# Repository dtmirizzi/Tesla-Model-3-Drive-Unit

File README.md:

# Tesla-Model-3-Drive-Unit
Open Source logic board for the Tesla Model 3 rear drive unit. PCB Files in DesignSpark 9 and Kicad 8 format.Based on the inverter designed by Johannes Heubner using FOC control.
<br>

<br>
13/03/20 : Added CAN logs from both CAN busses from the rear drive unit inverter powered on the bench.

04/05/20 : Added pdf schematic and board layout for the V1 logic board design. Untested as of this date. Given recent developments the design files will not be released at this time. For more information see : <br>
https://openinverter.org/forum/viewtopic.php?f=10&t=575

26/07/20 : After initial testing of V1 in a rear drive unit inverter some issues were found. V2 now released. Changes :

-Added resolver signal preconditioning circuit. Resolver signal needs to be amplified to 1v p-p and offset to 1.6v before feeding to the Tesla resolvver power amp.

-Added opamp to combine differential HV voltage measurement to unipolar.

-Deleted Tagconnect Jtag.

-Added 3v3 pin for single wire programming via st-link.

-Added solder jumper for optional single 5v power supply.

Please note design source files will be only available via Patreon for a period of time:

https://www.patreon.com/evbmw

02/10/20 : V2 board now fully tested in an M3 Rear drive unit and working very well on the bench.
<br>At this time I have decided to do a full opensource release of all design sources:)
<br>More updates and video to following including testing in a M3 front DU.

18/11/20 : Uploaded spreadsheet work in progress for mapping the pin assignments of the TMS320F28377D MCU.

21/11/20 : Discovered an eeprom on the back of the pcb. Logic analyser captures uploaded. All logic analyser captures made using Saleae logic. Free software available here :https://www.saleae.com/downloads/

02/12/20 : Big thanks to Colin Kidder (https://github.com/collin80) for the explanation of the STGAP1AS SPI gate driver traffic. PDF uploaded to the Gate SPI folder.

11/12/20 : Big thanks again to Colin Kidder (https://github.com/collin80) for the explanation of the TLF SPI power supply traffic. PDF uploaded to the TLF SPI folder.

08/02/21 : We have a new modboard : https://vimeo.com/509198907

08/05/21 : Added V3 modboard pdf schematic and board layout. Turns out Mr.Musk almost made a fool of me....again! 

18/10/21 : Added design files for USB to JTAG adapter board.

19/03/23 : Add first temp sensor calibration data

30/03/23 : Running : https://vimeo.com/809120859

15/08/24 : Added a very early schematic of the gate driver section for use in the PCB replacement project.

24/10/24 : Updated schematic of the gate driver power supply section for use in the PCB replacement project.

17/01/25 : Updated schematic and PCB layout to latest "complete" V1 version.

07/05/25 : First prototypes undergoing test.

28/05/25 : Testing continues. First motor spins :

https://youtu.be/JKbsiIRJ8mo

29/09/25 : V2 board now runs on HV : https://vimeo.com/1122427765

Added V3 Schematic and board layout.

26/10/25 : The V3 works. https://youtu.be/QYh9N8k0tf8

18/11/25 : First in car tests : https://youtu.be/6yrDDHRgUPQ also added pinout diagram.

03/12/25 : Updated 30 pin connector pinout and added a DXF of the OEM board derived from a laser scan.

01/02/26 : Uploaded V3.2 schematic and pcb layout. First order of boards on the way!

26/02/26 : Added capture of the gate driver SPI from a Model 3 front drive unit inverter.

28/02/26 : V3.2 board now undergoing testing.

07/03/26 : I have made the decision to fully opensource the V3.2 design. Almost six years of work in here by myself and others so please respect that.

09/04/26 : An amazing contribution : https://github.com/jrbe/Tesla-Model-3-Current-Sensor-Block
           Prototypes on order.

atopile port: [`ato/`](ato/README.md) describes the V3.2 board as code, organised into modules with one shared gate-driver phase. It is checked pad by pad against the KiCad design and keeps the original layout.

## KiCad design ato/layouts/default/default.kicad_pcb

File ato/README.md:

# M3DU logic board in atopile

An [atopile](https://atopile.io) port of the V3.2 logic board in
`../Design/M3DU_BoardV3_2`. It is the same board, checked pad by pad: the same
798 parts, designators, nets, BOM and hand-routed layout. It is organised into
modules, one per block of the schematic, and the three gate-driver phases share
one `GateDrivePhase` module. See [PLAN.md](PLAN.md) for details and next steps.

## Layout

```
ato.yaml                 atopile project (requires atopile ^0.15.9)
main.ato                 module M3DU: the blocks, power rails and nets between blocks
src/                     one module per schematic block (power/, gate_drive/, sensing/, ...)
parts/<KiCadLib>/        one atopile component per BOM line + its footprint/symbol
layouts/default/         the KiCad board atopile builds into (seeded from the original PCB)
lib/                     footprint + symbol libraries recovered from the KiCad design
reference/netlist.json   reference netlist extracted from the original PCB
reference/addresses.json designator -> atopile address (binds the layout)
tools/                   extraction, code generation, layout seeding and the equivalence check
```

## Build

```bash
uv venv -p 3.14 .venv && . .venv/bin/activate
uv pip install atopile==0.15.9 pandas xlrd

tools/port.sh            # extract -> generate -> seed layout -> ato build -> check
# or, once seeded:
ato build --no-standardize-designators
python tools/restore_layout.py  # put back attributes atopile 0.15.9 drops
python tools/check_netlist.py   # board vs KiCad V3.2: nets + layout
python tools/check_bom.py       # BOM vs the V3.2 JLC BOM
```

`main.ato`, `src/` and `parts/` are generated by `tools/gen_modules.py` (set
`FLAT=1` for a single flat module). The board stays bound to the layout through
the original designators.

`check_netlist.py` exits non-zero unless the built board matches the original:
the same references and pad geometry, the same pad-to-net partition, and every
footprint, track, via and zone in place.

Open `layouts/default/default.kicad_pcb` in KiCad 9 to view or edit the board.
After editing the layout, run `tools/port.sh --no-seed` so your edits are kept.
For now the original KiCad project is still the source of truth: `tools/port.sh`
and CI regenerate everything from it.

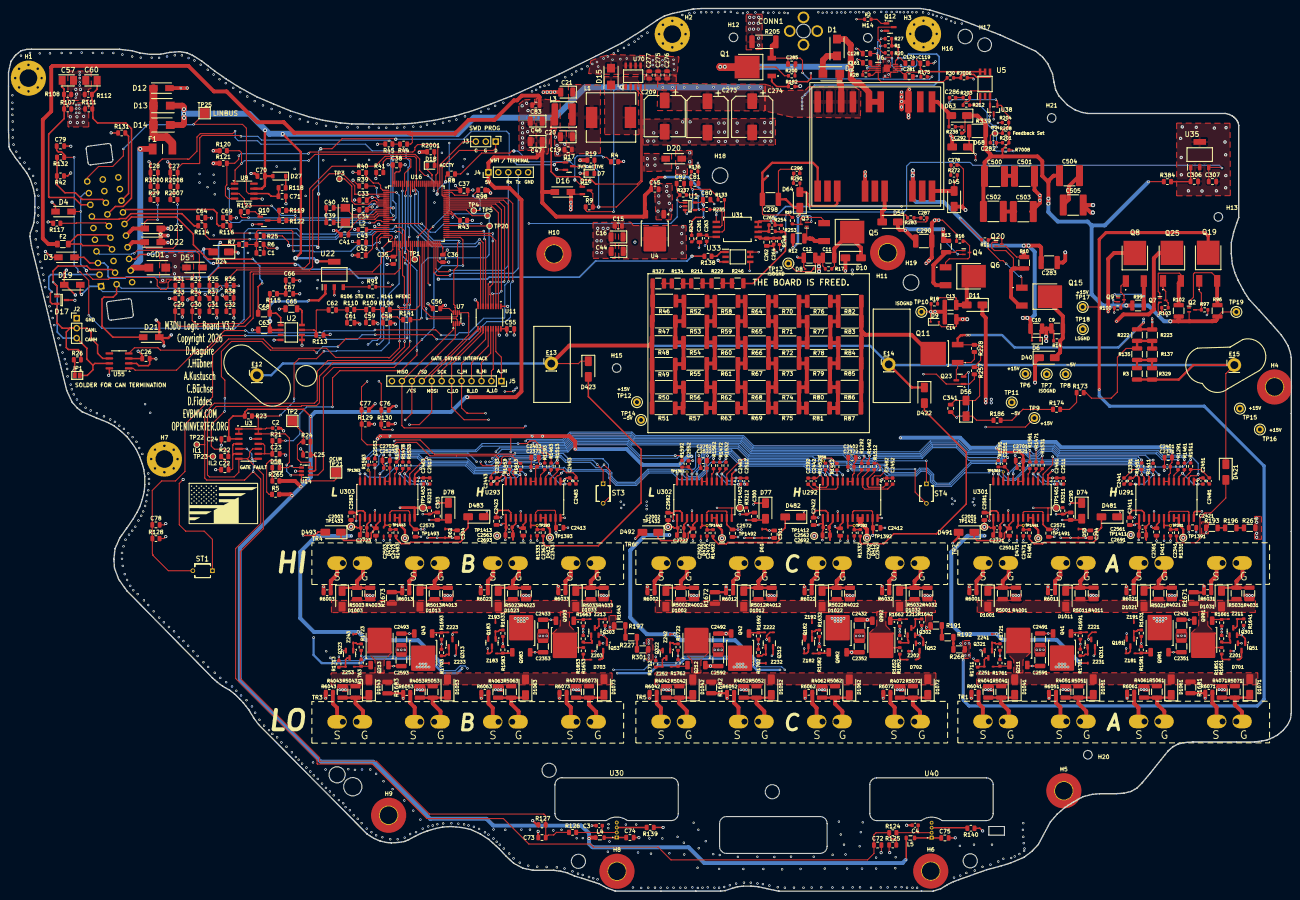
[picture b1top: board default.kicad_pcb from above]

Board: 4 copper layers, 327.6 x 225.4 mm, 797 parts (1 on the bottom side), 394 nets.

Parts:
C1, C306: 1uF; C_0805_2012Metric__v3
C2: 10nF; C_0603_1608Metric__v3
C3, C4, C265: 10nF; C_0603_1608Metric
C9, C10, C11, C12, C13, C14: 2.2uF; C_1210_3225Metric
C15, C19, C22, C24, C25, C27, C28, C34, C35, C36, C56, C70: 1uF; C_0805_2012Metric__v2
C16, C20, C21, C44: 100uF 6.3V; CP_EIA-3528-15_AVX-H__v2
C23, C29, C30, C31, C32, C37, C38, C45, C55, C74, C75, C76, C77, C78, C79, C80, C119, C276, C277, C301, C304, C341, C2361, C2362, C2363, C2411, C2412, C2413, C2421, C2422, C2423, C2501, C2502, C2503, C2571, C2572, C2573, C2581: 1uF; C_0805_2012Metric
C26, C41, C42: 100nF; C_0805_2012Metric
C33, C43, C261: 10uF; C_0805_2012Metric
C39, C40: 22pF; C_0805_2012Metric
C46, C47: 100uF 6.3V; CP_EIA-3528-15_AVX-H
C57: 100uF 6.3V; CAPPM3528X210N
C58, C59, C61, C66, C67: 22nF; C_0805_2012Metric
C60: 100uF 6.3V; CAPPM3528X210N__v2
C62: 22nF; C_0805_2012Metric__v2
C63, C65: 10uF; C_1206_3216Metric__v2
C64, C69, C71, C72: 1nF; C_0805_2012Metric
C68: 10uF; C_1206_3216Metric
C73: 1nF; C_0805_2012Metric__v2
C81, C82: 100pF; C_0805_2012Metric
C83: 1nF; C_0805_2012Metric__v4
C124, C275: 0.1uF; C_0805_2012Metric
C128: 200pF; C_0805_2012Metric
C161: 47nF; C_0805_2012Metric
C209: 100uF 25V; CP_Elec_10x10
C262: 10uF; C_0805_2012Metric__v2
C263, C2001, C2002, C2003, C2371, C2372, C2373, C2521, C2522, C2523, C2561, C2562, C2563: 100nF; C_0603_1608Metric
C264: 100nF; C_0603_1608Metric__v2
C273, C274: 220uF 35V; CP_Elec_10x10
C278, C287, C292, C296, C2341, C2342, C2343, C2471, C2472, C2473: 82pF; C_0603_1608Metric
C281: 330pF; C_0805_2012Metric
C282: 10nF; C_0603_1608Metric__v2
C283, C290, C298: 3.3uF; C_1812_4532Metric
C285: 470pF; C_0805_2012Metric
C286: 22nF; C_0603_1608Metric__v2
C293, C294, C300, C303, C2582, C2583: 2.2uF; C_0805_2012Metric
C307: 10uF; C_0805_2012Metric__v3
C500, C501, C502, C503, C504, C505: 15uF; C_2220_5750Metric
C2351, C2352, C2353, C2431, C2432, C2433, C2491, C2492, C2493, C2591, C2592, C2593: 4.7uF; C_1210_3225Metric
C2391, C2392, C2393, C2451, C2452, C2453, C2461, C2462, C2463, C2481, C2482, C2483, C2511, C2512, C2513, C2551, C2552, C2553: 82pF; C_0603_1608Metric__v2
C2401, C2402, C2403, C2691, C2692, C2693, C2701, C2702, C2703, C2721, C2722, C2723: 4.7uF; C_0805_2012Metric
C2441, C2442, C2443: 470pF; C_0603_1608Metric__v2
CONN1: HV_Hvil; HV_HVIL
D1: 1N5819; DIOM5336X244N__v2
D2: 1N5935B; DIOM5336X244N__v2
D3, D4, D5, D19: SMAJ18CA; DIOM5127X229N
D6, D8: 5V1; D_SOD-323__v2
D7: 3V3 LED; LED_0805_2012Metric
D9: 5V1; D_SOD-323
D10, D40: SS35; D_SMA__v2
D11: SS35; D_SMA
D12: SMAJ18CA; DIONM5127X229N
D13, D14: SS54B; DIOM5336X244N
D15: SS54B; DIOM5336X244N__v2
D16, D22, D23: SMAJ7.0A; DIOM5026X229N
D17: ESDCAN01-2BLY; SOT95P255X150-3N
D18: LED; LED_0805_2012Metric
D20: SMAJ7.0A; DIOM5026X229N__v2
D21: SMAJ18CA; DIOM5127X229N__v2
D24: SMAJ18CA; D_SMA__v3
D27: 1N4148W; D_SOD-123
D45, D64: STPS2H100-Y; D_SMA__v2
D53, D61, D62: G1; D_SOD-323__v3
D54, D63: STPS2H100-Y; D_SMA
D56: 15V; D_SMA__v4
D58: LED; LED_0805_2012Metric__v2
D68: Zener 5V1; D_SMA
D74, D77, D78, D421, D422, D423: VN17; D_SMA
D411, D412, D413, D701, D702, D703: JV; D_SOD-323
D471, D472, D473: JV; D_SOD-323__v3
D481, D482, D483, D491, D492, D493: VN17; D_SMA__v2
D1001, D1002, D1003, D1011, D1012, D1013, D1021, D1022, D1023, D1031, D1032, D1033, D1041, D1042, D1043, D1051, D1052, D1053, D1061, D1062, D1063, D1071, D1072, D1073: 2H2; D_SMA
E12, E13, E14, E15: HV+; M3_HVPOS
F1: JFC2410-0500TS; FUSC6126X280N
F2: 1206L050/24WR; Fuse_1206_3216Metric
GD1: 2051-09-SM-RPLF; DIOM5336X244N
H1, H2, H3, H7: MountingHole_Pad; MountingHole_4.5mm_Pad_Via
H4, H5, H6, H8, H9, H10, H11: MountingHole_Pad; MountingHole_4.5mm_Pad_TopBottom
H12, H14, H15, H21: MountingHole; MountingHole_2.2mm_M2__v2
H13: MountingHole; MountingHole_2.2mm_M2__v3
H16: MountingHole; MountingHole_3.7mm
H17: MountingHole; MountingHole_3.5mm
H18, H19: MountingHole; MountingHole_4mm
H20: MountingHole; MountingHole_2.2mm_M2
J1: Conn_01x30_Male; M3DU_MAINCONN
J2: CAN MON; PinHeader_1x03_P2.54mm_Vertical
J3: M032.54MM; PinHeader_1x03_P2.54mm_Vertical
J4: WiFi Serial Interface; PinHeader_1x05_P2.54mm_Vertical
J5: Conn_01x12_Socket; PinSocket_1x12_P2.54mm_Vertical
JP1: SolderJumper_2_Open; SolderJumper-2_P1.3mm_Open_Pad1.0x1.5mm
L1: 68uH; L_12x12mm_H8mm
L2, L4, L5: 10uH; L_0805_2012Metric
L3: 3uH; L_APV_ANR6020
Q1: IPD50N06S409ATMA2
Q2, Q3, Q4, Q7, Q9, Q20: BC857BT-7-F; SOT50P160X90-3N
Q5, Q6, Q15: NJVMJD127T4G; NVD5117PLT4GVF01__v2
Q8, Q19, Q25: NJVMJD127T4G; NVD5117PLT4GVF01
Q10, Q12: MMBT3904; SOT-23
Q11: FGD3N60LSDTM
Q16, Q17: MMBT3904; SOT-23__v3
Q23: BSS84W; SOT-23__v2
Q41, Q42, Q43, Q981, Q982, Q983: 45P4LLF6; TO-252-2
Q51, Q52, Q53: SG NMOS D; SOT-23
Q181, Q182, Q183: BSS84AK; SOT-23__v2
Q211, Q212, Q213, Q991, Q992, Q993: 3N0408; TO-252-2
Q301, Q302, Q303: BSS138BK; SOT-23__v2
Q311, Q312, Q313: BSS84AK; SOT-23
Q321, Q322, Q323: BSS138BK; SOT-23
R1, R133, R136, R235, R237: 10K; R_0603_1608Metric
R2: 3K3; R_0603_1608Metric
R3, R135, R137, R222, R223, R329: 82K; R_1210_3225Metric
R4: 10K; R_0805_2012Metric__v6
R5: 10K; R_0805_2012Metric__v9
R6: 1K5; R_0805_2012Metric__v3
R7: 4K7; R_0805_2012Metric__v3
R8, R25: 10K; R_0805_2012Metric__v3
R9: 27K; R_0805_2012Metric__v4
R10, R13, R99: 4R99; R_1210_3225Metric
R11, R16, R97, R100, R103: 22K; R_0603_1608Metric
R12, R96, R102: 4R99; R_1210_3225Metric__v2
R14, R17, R18: 4K7; R_0603_1608Metric
R15: 22K; R_0603_1608Metric__v2
R19: 680R; R_0805_2012Metric__v2
R20: 4R7; R_0603_1608Metric
R21, R22, R113, R114, R115, R116, R119, R128, R129, R130: 10K; R_0805_2012Metric__v2
R23, R24, R31, R32, R35, R36, R41: 4K7; R_0805_2012Metric__v2
R26: 120R; R_0805_2012Metric__v2
R27: 300K; R_0603_1608Metric
R28: 33.2K; R_0603_1608Metric__v2
R29, R39, R40, R43, R118, R123, R131, R132, R265, R2007, R2008, R3000: 1K; R_0805_2012Metric__v2
R30: 18K; R_0603_1608Metric
R33, R34, R37, R38: 1K5; R_0805_2012Metric__v2
R42, R44: 47K; R_0805_2012Metric__v2
R45, R122: 3K3; R_0805_2012Metric__v2
R46, R51, R56, R61, R66, R71, R76, R81, R82, R83, R84, R85, R86, R87: 3K9; R_2512_6332Metric
R47, R48, R49, R50, R52, R53, R54, R55, R57, R58, R59, R60, R62, R63, R64, R65, R67, R68, R69, R70, R72, R73, R74, R75, R77, R78, R79, R80: 3K9; R_2512_6332Metric__v2
R91: 1K; R_0603_1608Metric
R98: 1K; R_0805_2012Metric__v3
R106: 3K9; R_0805_2012Metric__v7
R107, R108, R112: 220R; R_0805_2012Metric__v2
R109, R110: 1K8; R_0805_2012Metric__v2
R111: 220R; R_0805_2012Metric
R117: 0R; R_0805_2012Metric__v2
R120, R121, R138: 2K2; R_0805_2012Metric__v2
R124, R126: 3K6; R_0805_2012Metric__v2
R125, R127: 6K2; R_0805_2012Metric__v2
R134, R211, R229, R246, R327: 75K; R_1210_3225Metric
R139, R140: 10k; R_0805_2012Metric__v5
R141: 3K9; R_0805_2012Metric__v8
R173, R174, R186: 50K; R_0805_2012Metric__v4
R175, R1331, R1332, R1333, R1411, R1412, R1413, R1461, R1462, R1463, R1471, R1472, R1473, R1481, R1482, R1483, R7006: 1k; R_0603_1608Metric
R182: 100K; R_0603_1608Metric__v2
R191, R192, R193, R196, R197, R227, R267, R268, R301: 1M; R_1206_3216Metric
R200: 20R; R_0603_1608Metric__v2
R201: 35K6; R_0603_1608Metric
R203, R212: 25K; R_0603_1608Metric
R204: 5K6; R_0603_1608Metric
R205: 0.01R; R_2512_6332Metric_Pad1.40x3.35mm_HandSolder
R208: 39K; R_0603_1608Metric
R228, R257: 100K; R_0805_2012Metric__v2
R238: 80.6R; R_0603_1608Metric__v2
R247, R248: 10R; R_0603_1608Metric
R253: 39R; R_0603_1608Metric
R254: 1K6; R_0603_1608Metric
R272, R283, R291: 80.6R; R_0603_1608Metric
R339: 4K7; R_1812_4532Metric
R384: 0R; R_0805_2012Metric__v4
R1291, R1292, R1293, R1561, R1562, R1563: 680; R_0603_1608Metric
R1451, R1452, R1453, R1511, R1512, R1513, R1531, R1532, R1533, R1641, R1642, R1643, R1711, R1712, R1713: 100; R_0603_1608Metric
R1581, R1582, R1583, R1631, R1632, R1633, R1651, R1652, R1661, R1662, R1663, R1691, R1692, R1693, R1701, R1702, R1703, R1761, R1762, R1763, R1853: 27K; R_0603_1608Metric
R1591, R1592, R1593: 200; R_0603_1608Metric
R1653, R1851, R1852: 470; R_0603_1608Metric
R1671, R1672, R1673: 4K7; R_1210_3225Metric__v2
R1681, R1682, R1683: 4K7; R_1210_3225Metric
R1721, R1722, R1723: 27K; R_0603_1608Metric__v3
R2001: 330R; R_0805_2012Metric__v2
R3211, R3212, R3213: 0R; R_0603_1608Metric
R4001, R4002, R4003, R4011, R4012, R4013, R4021, R4022, R4023, R4031, R4032, R4033, R4041, R4042, R4043, R4051, R4052, R4053, R4061, R4062, R4063, R4071, R4072, R4073: 12; R_1210_3225Metric
R5001, R5002, R5003, R5011, R5012, R5013, R5021, R5022, R5023, R5031, R5032, R5033, R5041, R5042, R5043, R5051, R5052, R5053, R5061, R5062, R5063, R5071, R5072, R5073: 10; R_1210_3225Metric
R6001, R6002, R6003, R6011, R6012, R6013, R6021, R6022, R6023, R6031, R6032, R6033, R6041, R6042, R6043, R6051, R6052, R6053, R6061, R6062, R6063, R6071, R6072, R6073: 0.56R; R_0805_2012Metric
R7008: 2K; R_0603_1608Metric
ST1, ST3, ST4: Thermistor; B59100C0140A070
T1: TDK_VGT; VGT22EPC-200S6A12
TP1, TP3, TP4, TP5, TP22, TP23, TP24: TestPoint; TestPoint_Pad_D1.0mm
TP2, TP21, TP25: TestPoint; TestPoint_Pad_2.5x2.5mm
TP6, TP7, TP8, TP9, TP11, TP12, TP13, TP14, TP15, TP16, TP17, TP18, TP19: TestPoint; TestPoint_Keystone_5000-5004_Miniature
TP10: GND_ISO_C; TestPoint_Keystone_5000-5004_Miniature
TP20: TestPoint_Pad_D1.0mm
TP58, TP291, TP292, TP293, TP1361, TP1362, TP1363, TP1441, TP1442, TP1443: TestPoint; TestPoint_Via
TP1391, TP1392, TP1393, TP1411, TP1412, TP1413, TP1431, TP1432, TP1433, TP1451, TP1452, TP1453, TP1491, TP1492, TP1493: TestPoint; TestPoint_Pad_D1.5mm
TR1, TR2, TR3, TR4, TR5: M3DU_MOSFETS; M3DU_Mosfets
TR6: CH1234; M3DU_Mosfets
U1: OPA320AIDBVR; SOT95P280X145-5N
U2: TDA2822D013TR; SOIC127P600X175-8N
U3: LM2901; SOIC-14_3.9x8.7mm_P1.27mm
U4: LD1086DT33TR; TO-252-2
U5, U33: ACPL-M49T-000E; SOIC127P700X260-6N
U6: TPS40210DGQR; SOP50P490X110-11N
U7: 74LVC3G17; VSSOP-8_2.3x2mm_P0.5mm
U8: TJA1021T; SOIC-8_3.9x4.9mm_P1.27mm
U11: SN74LVC245APW; TSSOP-20_4.4x6.5mm_P0.65mm
U14: 74LVC1G10; SOT-23-6
U16: STM32F103VCTx; LQFP-100_14x14mm_P0.5mm
U22: NCV8452STT3G; SOT230P700X180-4N__v2
U30, U40: MLX91209LVA-CAA-000-SP; SIP_4L_VA
U31: ACPL-C87A; SSO-8_6.8x5.9mm_P1.27mm_Clearance8mm
U35: TLE4264G; SOT230P700X180-4N
U38: TL432AQDBZRQ1; SOT95P237X112-3N
U55: SN65HVD230; SOIC-8_3.9x4.9mm_P1.27mm__v2
U70: XL1509-5.0E1; SOIC127P600X175-8N
U291, U302: STGAP1AS; SOIC-24W_7.5x15.4mm_P1.27mm
U292: STGAP1AS; SOIC-24W_7.5x15.4mm_P1.27mm__v2
U293, U301, U303: STGAP1AS; SOIC-24W_7.5x15.4mm_P1.27mm__v3
X1: X50328MSB2GI; Crystal_SMD_5032-2Pin_5.0x3.2mm
Z181, Z182, Z183, Z201, Z202, Z203, Z211, Z212, Z213, Z221, Z222, Z223, Z251, Z252, Z253: 8.2V; D_SOD-323
Z191, Z192, Z193, Z241, Z242, Z243: 8.2V; D_SOD-323__v3
Z231, Z232, Z233: 8.2V; D_SOD-323__v2

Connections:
+3.3VA: C42.2, C43.2, L2.2, U16.21, U16.22
+3V3: C15.1, C16.1, C26.1, C33.2, C34.1, C35.1, C36.1, C37.1, C38.1, C44.1, C55.1, C56.1, C2371.2, C2372.2, C2373.2, C2401.2, C2402.2, C2403.2, C2521.2, C2522.2, C2523.2, C2701.2, C2702.2, C2703.2, D20.1, L2.1, R19.1, R39.1, R40.1, R43.1, R98.1, R107.2, R111.2, R120.1, R121.1, R131.1, R2001.1, ST1.1, ST3.1, ST4.1, U4.2, U7.8, U11.1, U11.20, U16.6, U16.11, U16.28, U16.50, U16.75, U16.100, U55.3, U291.6, U291.7, U292.6, U292.7, U293.6, U293.7, U301.6, U301.7, U302.6, U302.7, U303.6, U303.7
+5V: C24.1, C25.1, C45.1, C46.1, C47.1, C80.1, C83.1, D16.1, F2.2, J4.1, L3.2, L4.1, L5.1, R5.1, R23.2, R24.2, R44.1, R247.1, R265.2, U1.5, U3.3, U4.3, U14.5, U70.3
+5VP: C307.1, R248.2, U35.3
+12P: F1.1, GD1.2, J1.22
+12V: C70.1, C124.1, C209.1, C273.1, C274.1, C275.1, C276.1, C277.1, D2.2, D13.1, D14.1, D27.2, R1.2, R9.1, R27.1, R119.1, T1.6, T1.7, T1.8, T1.9, U6.10, U8.7, U22.4, U70.1
+15VH: C341.1, D56.1, Q23.2, R186.1, U33.5, U33.6
/5Vunfil: C19.1, C20.1, C21.1, L1.2, L3.1
/ASC_L: R3211.1, R3212.1, R3213.1, TP1451.1, TP1452.1, TP1453.1, U301.24, U302.24, U303.24
/CANH: D17.1, J1.12, J2.3, JP1.2, U55.7
/CANL: D17.2, J1.2, J2.2, R26.2, U55.6
/GATE_CS: J5.10, R1461.2, R1462.2, R1463.2, R1471.2, R1472.2, R1473.2, U7.2
/GATE_DIAG: D58.1, R5.2, TP1361.1, TP1362.1, TP1363.1, U14.1, U291.10, U292.10, U293.10, U301.10, U302.10, U303.10
/GATE_SD: J5.9, R1451.2, R1452.2, R1453.2, TP58.1, U7.5
/GATE_SPI_MISO: J5.11, U7.1, U291.2
/GATE_SPI_MOSI: J5.8, R1533.2, U11.11
/GATE_SPI_SCK: J5.7, R1291.2, R1292.2, R1293.2, R1561.2, R1562.2, R1563.2, U11.12
/GND_ISO_A: C9.1, C10.2, C2341.2, C2351.2, C2361.2, C2411.2, C2421.2, C2431.1, C2561.1, C2691.1, D6.1, D411.2, D481.1, R14.2, R1671.2, R6001.1, R6011.1, R6021.1, R6031.1, TP7.1, TP1411.1, U291.13, U291.16, U291.24
/GND_ISO_B: C11.1, C12.2, C2343.2, C2353.2, C2363.2, C2413.2, C2423.2, C2433.1, C2563.1, C2693.1, D8.1, D413.2, D483.1, R17.2, R1673.2, R6003.1, R6013.1, R6023.1, R6033.1, TP13.1, TP1413.1, U293.13, U293.16, U293.24
/GND_ISO_C: C13.1, C14.2, C2342.2, C2352.2, C2362.2, C2412.2, C2422.2, C2432.1, C2562.1, C2692.1, D9.1, D412.2, D482.1, R18.2, R1672.2, R6002.1, R6012.1, R6022.1, R6032.1, TP10.1, TP1412.1, U292.13, U292.16, U292.24
/HV+: D421.1, D422.1, D423.1, E12.1, E13.1, E14.1, E15.1, R3.2, R46.2, R47.2, R48.2, R49.2, R50.2, R51.2, R327.1, R329.2
/LIN_BUS: C71.1, J1.10, R118.2, TP25.1, U8.6
/PWMA_HI: J5.1, R1411.2, U11.18
/PWMA_LO: J5.2, R1591.2, U11.17
/PWMB_HI: J5.3, R1413.2, U11.16
/PWMB_LO: J5.4, R1593.2, U11.15
/PWMC_HI: J5.5, R1412.2, U11.14
/PWMC_LO: J5.6, R1592.2, U11.13
/SDI_A: R1531.2, U292.2
/SDI_C: R1532.2, U293.2
/VH_HS_A: C2351.1, C2361.1, D40.1, Q181.2, Q981.3, R1581.2, R1631.1, TP6.1, U291.17
/VH_HS_B: C2353.1, C2363.1, D10.1, Q183.2, Q983.3, R1583.2, R1633.1, TP12.1, U293.17
/VH_HS_C: C2352.1, C2362.1, D11.1, Q182.2, Q982.3, R1582.2, R1632.1, TP9.1, U292.17
/VH_LS: D491.2, D492.2, D493.2
/VH_LS_A: C2491.1, C2501.1, D74.1, D491.1, Q41.3, Q311.2, R1691.2, R1701.1, U301.17
/VH_LS_A_PRI: C293.1, D74.2, Q19.2, TP17.1
/VH_LS_B: C2493.1, C2503.1, D78.1, D493.1, Q43.3, Q313.2, R1693.2, R1703.1, U303.17
/VH_LS_B_PRI: C303.1, D78.2, Q25.2, TP15.1
/VH_LS_C: C2492.1, C2502.1, D77.1, D492.1, Q42.3, Q312.2, R1692.2, R1702.1, U302.17
/VH_LS_C_PRI: C300.1, D77.2, Q8.2, TP16.1
/VL_HS_A: C10.1, C283.2, C2411.1, C2421.1, C2431.2, D6.2, Q51.1, Q301.2, Q991.3, R11.2, R1651.2, R1661.1, T1.16, TP8.1, U291.14, U291.19, U291.23
/VL_HS_B: C12.1, C298.2, C2413.1, C2423.1, C2433.2, D8.2, Q53.1, Q303.2, Q993.3, R15.2, R1663.1, R1853.2, T1.10, TP14.1, U293.14, U293.19, U293.23
/VL_HS_C: C14.1, C290.2, C2412.1, C2422.1, C2432.2, D9.2, Q52.1, Q302.2, Q992.3, R16.2, R1652.2, R1662.1, T1.13, TP11.1, U292.14, U292.19, U292.23
ACCEL1: D23.1, J1.25, R29.2
ACCEL2: D22.1, J1.24, R2007.2
ACT_DISCH: D24.2, J1.23, R138.2
BMS_IN: TP5.1, U16.65
BRAKE: D21.1, J1.11, R36.2
BRAKE_IN: C32.1, R36.1, R38.2, U16.3
CAN_RX: U16.70, U55.4
CAN_TX: U16.71, U55.1
COSA: C57.1, J1.8, R107.1, R108.2
COSB: J1.27, R116.2
DCSW_OUT: TP3.1, U16.7
DESAT: R98.2, TP4.1, U16.66
EMCYSTOP_IN: R43.2, U16.64
ENC_A: C64.1, R114.1, U16.31
ENC_B: C69.1, R116.1, U16.32
EXCA: C68.2, J1.26
EXCB: J1.16, R117.1
EXC_OUT: R106.2, U16.83
FORW_IN: D4.1, J1.9, R31.2
FWD_IN: C29.1, R31.1, R33.2, U16.29
GATE PSU EN: R2.1, R91.2, U16.44
GATEDRV_CS: U7.6, U16.41
GATEDRV_SD: U7.3, U16.42
GND: C1.2, C2.2, C3.2, C4.2, C15.2, C16.2, C19.2, C20.2, C21.2, C22.2, C23.2, C24.2, C25.2, C26.2, C27.2, C28.2, C29.2, C30.2, C31.2, C32.2, C33.1, C34.2, C35.2, C36.2, C37.2, C38.2, C39.1, C40.1, C41.1, C42.1, C43.1, C44.2, C45.2, C46.2, C47.2, C55.2, C56.2, C57.2, C58.2, C59.2, C60.2, C61.2, C63.1, C64.2, C65.1, C66.2, C67.2, C69.2, C70.2, C71.2, C72.2, C73.2, C74.2, C75.2, C76.2, C77.2, C78.2, C79.2, C80.2, C81.2, C83.2, C119.2, C124.2, C128.2, C161.2, C209.2, C261.2, C263.1, C273.2, C274.2, C275.2, C276.2, C277.2, C281.2, C2371.1, C2372.1, C2373.1, C2391.2, C2392.2, C2393.2, C2401.1, C2402.1, C2403.1, C2441.2, C2442.2, C2443.2, C2451.2, C2452.2, C2453.2, C2461.2, C2462.2, C2463.2, C2481.2, C2482.2, C2483.2, C2511.2, C2512.2, C2513.2, C2521.1, C2522.1, C2523.1, C2551.2, C2552.2, C2553.2, C2701.1, C2702.1, C2703.1, D3.2, D4.2, D5.2, D7.1, D12.2, D15.2, D16.2, D17.3, D19.2, D20.2, D21.2, D22.2, D23.2, D24.1, GD1.1, H1.1, H2.1, H3.1, H7.1, J1.5, J1.6, J1.13, J2.1, J3.2, J4.5, Q10.2, Q12.2, Q16.2, Q17.2, R4.2, R6.1, R33.1, R34.1, R37.1, R38.1, R41.1, R42.1, R45.2, R108.1, R112.1, R113.1, R117.2, R125.1, R127.1, R128.2, R129.2, R130.2, R136.2, R139.1, R140.1, R182.2, R205.2, R2008.1, R3000.1, R7006.2, U1.2, U2.4, U2.5, U2.6, U3.12, U4.1, U6.6, U6.11, U7.4, U8.5, U11.10, U11.19, U14.2, U16.10, U16.19, U16.20, U16.27, U16.49, U16.74, U16.99, U22.2, U30.4, U31.5, U33.3, U40.4, U55.2, U55.8, U70.5, U70.6, U70.7, U70.8, U291.1, U291.12, U292.1, U292.12, U293.1, U293.12, U301.1, U301.12, U302.1, U302.12, U303.1, U303.12
HFEXC: R141.2, U16.63
HV-: C262.1, C264.2, C265.2, C293.2, C294.2, C300.2, C301.2, C303.2, C304.2, C306.2, C307.2, C341.2, C2001.1, C2002.1, C2003.1, C2471.2, C2472.2, C2473.2, C2491.2, C2492.2, C2493.2, C2501.2, C2502.2, C2503.2, C2571.2, C2572.2, C2573.2, C2581.2, C2582.2, C2583.2, C2591.1, C2592.1, C2593.1, C2721.1, C2722.1, C2723.1, D53.1, D56.2, D61.1, D62.1, D68.1, D471.2, D472.2, D473.2, Q11.3, R222.1, R223.1, R228.1, R254.2, R257.1, R267.2, R268.2, R301.2, R339.1, R1681.2, R1682.2, R1683.2, R3211.2, R3212.2, R3213.2, R6041.1, R6042.1, R6043.1, R6051.1, R6052.1, R6053.1, R6061.1, R6062.1, R6063.1, R6071.1, R6072.1, R6073.1, TP1431.1, TP1432.1, TP1433.1, U31.3, U31.4, U35.2, U35.4, U301.13, U301.16, U302.13, U302.16, U303.13, U303.16
IL1: C72.1, R124.1, R125.2, TP22.1, U3.5, U3.8, U16.30
IL2: C73.1, R126.1, R127.2, TP23.1, U3.7, U3.10, U16.35
LED_OUT: D18.1, U16.80
LIN_NSLP: U8.2, U16.9
LIN_Rx: R120.2, U8.1, U16.79
LIN_Tx: R121.2, U8.4, U16.78
LIN_WAKE: R123.1, U16.8
LS_+V: C292.1, C500.1, C502.1, C504.1, D63.1, Q2.2, Q7.2, Q9.2, R96.1, R99.1, R102.1, R201.2, R208.2, R339.2, R384.1, R7008.1, TP19.1
LS_GND: C294.1, C301.1, C304.1, C501.2, C503.2, C505.2, C2571.1, C2572.1, C2573.1, C2581.1, C2582.1, C2583.1, C2591.2, C2592.2, C2593.2, D53.2, D61.2, D62.2, D68.2, Q211.3, Q212.3, Q213.3, Q321.2, Q322.2, Q323.2, R97.2, R100.2, R103.2, R204.1, R1721.2, R1722.2, R1723.2, R1761.1, R1762.1, R1763.1, T1.3, TP18.1, U38.3, U301.14, U301.19, U301.23, U302.14, U302.19, U302.23, U303.14, U303.19, U303.23
MAIN_PSU_EN: R8.2, U16.77
MOT_NTC1: J1.28, R131.2
MOT_NTC2: J1.18, R42.2, R132.2
MPROT_IN: R39.2, U16.4
unnamed: C58.1, R106.1, R109.2, R141.1
unnamed: C59.1, R109.1, R110.2
unnamed: C61.1, C62.1, R110.1
unnamed: C66.1, C67.1, R115.1
unnamed: C278.1, R272.1
unnamed: C285.1, R200.2
unnamed: C286.2, R203.1
unnamed: C287.1, R283.1
unnamed: C292.2, R238.2
unnamed: C296.1, R291.1
unnamed: C500.2, C501.1
unnamed: C502.2, C503.1
unnamed: C504.2, C505.1
unnamed: D1.2, Q1.2, R200.1, T1.4, T1.5
unnamed: D1.1, D2.1
unnamed: D7.2, R19.2
unnamed: C11.2, D10.2, Q5.2, R17.1
unnamed: C13.2, D11.2, Q6.2, R18.1
unnamed: D12.1, D13.2, D14.2, F1.2
unnamed: D18.2, R2001.2
unnamed: D27.1, R118.1
unnamed: C9.2, D40.2, Q15.2, R14.1
unnamed: D45.2, R272.2, T1.18
unnamed: C278.2, C283.1, D45.1, Q20.2, R10.1
unnamed: D54.2, R283.2, T1.15
unnamed: C287.2, C290.1, D54.1, Q4.2, R13.1
unnamed: D58.2, R265.1
unnamed: D63.2, R238.1, T1.1
unnamed: D64.2, R291.2, T1.12
unnamed: C296.2, C298.1, D64.1, Q3.2, R12.1
unnamed: C2341.1, D411.1, R1331.1, TP291.1, U291.18
unnamed: C2342.1, D412.1, R1332.1, TP292.1, U292.18
unnamed: C2343.1, D413.1, R1333.1, TP293.1, U293.18
unnamed: D421.2, R1331.2
unnamed: D422.2, R1332.2
unnamed: D423.2, R1333.2
unnamed: C2471.1, D471.1, R1481.1, TP1441.1, U301.18
unnamed: C2472.1, D472.1, R1482.1, TP1442.1, U302.18
unnamed: C2473.1, D473.1, R1483.1, TP1443.1, U303.18
unnamed: D481.2, R1481.2
unnamed: D482.2, R1482.2
unnamed: D483.2, R1483.2
unnamed: D701.2, R1851.1
unnamed: D701.1, Q51.3
unnamed: D702.2, R1852.1
unnamed: D702.1, Q52.3
unnamed: D703.2, R1653.1
unnamed: D703.1, Q53.3
unnamed: D1001.2, D1011.2, D1021.2, D1031.2, Q991.2, R1671.1, R1851.2, R5001.1, R5011.1, R5021.1, R5031.1
unnamed: D1001.1, R4001.2, R5001.2, TR2.2
unnamed: D1002.2, D1012.2, D1022.2, D1032.2, Q992.2, R1672.1, R1852.2, R5002.1, R5012.1, R5022.1, R5032.1
unnamed: D1002.1, R4002.2, R5002.2, TR6.2
unnamed: D1003.2, D1013.2, D1023.2, D1033.2, Q993.2, R1653.2, R1673.1, R5003.1, R5013.1, R5023.1, R5033.1
unnamed: D1003.1, R4003.2, R5003.2, TR4.2
unnamed: D1011.1, R4011.2, R5011.2, TR2.4
unnamed: D1012.1, R4012.2, R5012.2, TR6.4
unnamed: D1013.1, R4013.2, R5013.2, TR4.4
unnamed: D1021.1, R4021.2, R5021.2, TR2.6
unnamed: D1022.1, R4022.2, R5022.2, TR6.6
unnamed: D1023.1, R4023.2, R5023.2, TR4.6
unnamed: D1031.1, R4031.2, R5031.2, TR2.8
unnamed: D1032.1, R4032.2, R5032.2, TR6.8
unnamed: D1033.1, R4033.2, R5033.2, TR4.8
unnamed: D1041.2, D1051.2, D1061.2, D1071.2, Q211.2, R1681.1, R5041.1, R5051.1, R5061.1, R5071.1
unnamed: D1041.1, R4041.2, R5041.2, TR1.2
unnamed: D1042.2, D1052.2, D1062.2, D1072.2, Q212.2, R1682.1, R5042.1, R5052.1, R5062.1, R5072.1
unnamed: D1042.1, R4042.2, R5042.2, TR5.2
unnamed: D1043.2, D1053.2, D1063.2, D1073.2, Q213.2, R1683.1, R5043.1, R5053.1, R5063.1, R5073.1
unnamed: D1043.1, R4043.2, R5043.2, TR3.2
unnamed: D1051.1, R4051.2, R5051.2, TR1.4
unnamed: D1052.1, R4052.2, R5052.2, TR5.4
unnamed: D1053.1, R4053.2, R5053.2, TR3.4
unnamed: D1061.1, R4061.2, R5061.2, TR1.6
unnamed: D1062.1, R4062.2, R5062.2, TR5.6
unnamed: D1063.1, R4063.2, R5063.2, TR3.6
unnamed: D1071.1, R4071.2, R5071.2, TR1.8
unnamed: D1072.1, R4072.2, R5072.2, TR5.8
unnamed: D1073.1, R4073.2, R5073.2, TR3.8
unnamed: F2.1, J1.14, J1.15
unnamed: JP1.1, R26.1
unnamed: Q1.1, R20.1, R182.1
unnamed: C285.2, Q1.3, R175.2, R205.1
unnamed: Q3.1, Q5.3, R12.2
unnamed: Q3.3, Q5.1, R15.1
unnamed: Q4.1, Q6.3, R13.2
unnamed: Q4.3, Q6.1, R16.1
unnamed: Q8.1, Q9.3, R100.1
unnamed: Q8.3, Q9.1, R99.2
unnamed: Q10.1, R123.2
unnamed: Q10.3, R119.2, R122.1
unnamed: Q11.2, R82.1, R83.1, R84.1, R85.1, R86.1, R87.1
unnamed: Q11.1, Q23.3, R228.2
unnamed: Q12.1, R2.2
unnamed: Q12.3, R1.1, U6.3
unnamed: Q15.1, Q20.3, R11.1
unnamed: Q15.3, Q20.1, R10.2
unnamed: Q16.1, R4.1, R8.1
unnamed: Q16.3, Q17.3, R9.2, U70.4
unnamed: Q17.1, R25.1
unnamed: Q2.3, Q19.1, R97.1
unnamed: Q2.1, Q19.3, R96.2
unnamed: Q23.1, R257.2, U33.4
unnamed: Q7.3, Q25.1, R103.1
unnamed: Q7.1, Q25.3, R102.2
unnamed: Q41.2, R4041.1, R4051.1, R4061.1, R4071.1
unnamed: Q41.1, R1691.1, Z221.1
unnamed: Q42.2, R4042.1, R4052.1, R4062.1, R4072.1
unnamed: Q42.1, R1692.1, Z222.1
unnamed: Q43.2, R4043.1, R4053.1, R4063.1, R4073.1
unnamed: Q43.1, R1693.1, Z223.1
unnamed: Q51.2, R193.1
unnamed: Q52.2, R191.1
unnamed: Q53.2, R197.1
unnamed: Q181.3, R1641.1, Z181.2
unnamed: Q181.1, R1631.2, Z191.1
unnamed: Q182.3, R1642.1, Z182.2
unnamed: Q182.1, R1632.2, Z192.1
unnamed: Q183.3, R1643.1, Z183.2
unnamed: Q183.1, R1633.2, Z193.1
unnamed: Q211.1, R1761.2, Z251.2
unnamed: Q212.1, R1762.2, Z252.2
unnamed: Q213.1, R1763.2, Z253.2
unnamed: Q301.3, R1641.2, Z211.1
unnamed: Q301.1, R1651.1, Z201.2
unnamed: Q302.3, R1642.2, Z212.1
unnamed: Q302.1, R1652.1, Z202.2
unnamed: Q303.3, R1643.2, Z213.1
unnamed: Q303.1, R1853.1, Z203.2
unnamed: Q311.3, R1711.1, Z221.2
unnamed: Q311.1, R1701.2, Z231.1
unnamed: Q312.3, R1712.1, Z222.2
unnamed: Q312.1, R1702.2, Z232.1
unnamed: Q313.3, R1713.1, Z223.2
unnamed: Q313.1, R1703.2, Z233.1
unnamed: Q321.3, R1711.2, Z251.1
unnamed: Q321.1, R1721.1, Z241.2
unnamed: Q322.3, R1712.2, Z252.1
unnamed: Q322.1, R1722.1, Z242.2
unnamed: Q323.3, R1713.2, Z253.1
unnamed: Q323.1, R1723.1, Z243.2
unnamed: Q981.2, R4001.1, R4011.1, R4021.1, R4031.1
unnamed: Q981.1, R1581.1, Z181.1
unnamed: Q982.2, R4002.1, R4012.1, R4022.1, R4032.1
unnamed: Q982.1, R1582.1, Z182.1
unnamed: Q983.2, R4003.1, R4013.1, R4023.1, R4033.1
unnamed: Q983.1, R1583.1, Z183.1
unnamed: Q991.1, R1661.2, Z211.2
unnamed: Q992.1, R1662.2, Z212.2
unnamed: Q993.1, R1663.2, Z213.2
unnamed: R24.1, TP2.1, U14.6
unnamed: R46.1, R47.1, R48.1, R49.1, R50.1, R51.1, R52.2, R53.2, R54.2, R55.2, R56.2, R57.2
unnamed: R52.1, R53.1, R54.1, R55.1, R56.1, R57.1, R58.2, R59.2, R60.2, R61.2, R62.2, R63.2
unnamed: R58.1, R59.1, R60.1, R61.1, R62.1, R63.1, R64.2, R65.2, R66.2, R67.2, R68.2, R69.2
unnamed: R64.1, R65.1, R66.1, R67.1, R68.1, R69.1, R70.2, R71.2, R72.2, R73.2, R74.2, R75.2
unnamed: R70.1, R71.1, R72.1, R73.1, R74.1, R75.1, R76.2, R77.2, R78.2, R79.2, R80.2, R81.2
unnamed: R76.1, R77.1, R78.1, R79.1, R80.1, R81.1, R82.2, R83.2, R84.2, R85.2, R86.2, R87.2
unnamed: R134.1, R327.2
unnamed: R134.2, R211.1
unnamed: R135.1, R137.1, R173.2, R222.2, R223.2
unnamed: R3.1, R135.2, R137.2, R329.1
unnamed: R173.1, R174.2
unnamed: R174.1, R186.2
unnamed: R191.2, R192.1
unnamed: R192.2, R268.1
unnamed: R193.2, R196.1
unnamed: R196.2, R267.1
unnamed: R197.2, R227.1
unnamed: R211.2, R229.2
unnamed: R227.2, R301.1
unnamed: R229.1, R246.2
unnamed: R246.1, R253.2, R254.1
unnamed: R6041.2, TR1.1
unnamed: R6051.2, TR1.3
unnamed: R6061.2, TR1.5
unnamed: R6071.2, TR1.7
unnamed: R6001.2, TR2.1
unnamed: R6011.2, TR2.3
unnamed: R6021.2, TR2.5
unnamed: R6031.2, TR2.7
unnamed: R6043.2, TR3.1
unnamed: R6053.2, TR3.3
unnamed: R6063.2, TR3.5
unnamed: R6073.2, TR3.7
unnamed: R6003.2, TR4.1
unnamed: R6013.2, TR4.3
unnamed: R6023.2, TR4.5
unnamed: R6033.2, TR4.7
unnamed: R6042.2, TR5.1
unnamed: R6052.2, TR5.3
unnamed: R6062.2, TR5.5
unnamed: R6072.2, TR5.7
unnamed: R6002.2, TR6.1
unnamed: R6012.2, TR6.3
unnamed: R6022.2, TR6.5
unnamed: R6032.2, TR6.7
unnamed: C81.1, R133.1, R136.1, U1.3
unnamed: C82.2, R235.1, R237.2, U1.4
unnamed: C62.2, R113.2, U2.7
unnamed: C65.2, U2.8
unnamed: C68.1, R115.2, U2.1
unnamed: C63.2, U2.2, U22.1
unnamed: C22.1, R22.1, U3.4, U3.6
unnamed: C23.1, R21.1, U3.9, U3.11
unnamed: R212.1, R7008.2, U5.1
unnamed: R30.2, R7006.1, U5.4
unnamed: C119.1, U5.5, U5.6, U6.9
unnamed: R28.1, U6.4
unnamed: R28.2, R30.1, U6.5
unnamed: R20.2, U6.8
unnamed: C281.1, R175.1, U6.7
unnamed: C128.1, R27.2, U6.1
unnamed: C161.1, U6.2
unnamed: R122.2, U8.3
unnamed: R41.2, U16.94
unnamed: C41.2, U16.14
unnamed: C40.2, U16.12, X1.2
unnamed: C39.2, U16.13, X1.1
unnamed: R44.2, R45.1, U16.34
unnamed: TP20.1, U16.57
unnamed: R91.1, U22.3
unnamed: C3.1, R126.2, U30.2
unnamed: R139.2, U30.3
unnamed: C74.1, L4.2, U30.1
unnamed: C265.1, R253.1, U31.2
unnamed: R133.2, U31.7
unnamed: R235.2, U31.6
unnamed: C262.2, C264.1, R248.1, U31.1
unnamed: C261.1, C263.2, R247.2, U31.8
unnamed: R138.1, U33.1
unnamed: C306.1, R384.2, U35.1
unnamed: C282.2, R201.1, R203.2, R212.2, U5.3, U38.2
unnamed: C282.1, C286.1, R204.2, R208.1, TP24.1, U38.1
unnamed: C4.1, R124.2, U40.2
unnamed: R140.2, U40.3
unnamed: C75.1, L5.2, U40.1
unnamed: D15.1, L1.1, U70.2
unnamed: R1291.1, U291.5
unnamed: TP1391.1, U291.20, U291.21, Z191.2, Z201.1
unnamed: C2391.1, R1411.1, U291.9, U301.8
unnamed: C2551.1, R1591.1, U291.8, U301.9
unnamed: C2481.1, R1511.1, U291.3
unnamed: C2561.2, C2691.2, U291.15
unnamed: C2451.1, R1461.1, U291.4
unnamed: C2441.1, R1451.1, U291.11, U301.11
unnamed: R1292.1, U292.5
unnamed: TP1392.1, U292.20, U292.21, Z192.2, Z202.1
unnamed: C2392.1, R1412.1, U292.9, U302.8
unnamed: C2552.1, R1592.1, U292.8, U302.9
unnamed: C2482.1, R1512.1, U292.3
unnamed: C2562.2, C2692.2, U292.15
unnamed: C2452.1, R1462.1, U292.4
unnamed: C2442.1, R1452.1, U292.11, U302.11
unnamed: R1293.1, U293.5
unnamed: TP1393.1, U293.20, U293.21, Z193.2, Z203.1
unnamed: C2393.1, R1413.1, U293.9, U303.8
unnamed: C2553.1, R1593.1, U293.8, U303.9
unnamed: C2483.1, R1513.1, U293.3
unnamed: C2563.2, C2693.2, U293.15
unnamed: C2453.1, R1463.1, U293.4
unnamed: C2443.1, R1453.1, U293.11, U303.11
unnamed: R1561.1, U301.5
unnamed: TP1491.1, U301.20, U301.21, Z231.2, Z241.1
unnamed: C2511.1, R1531.1, U301.3
unnamed: R1511.2, U301.2
unnamed: C2001.2, C2721.2, U301.15
unnamed: C2461.1, R1471.1, U301.4
unnamed: R1562.1, U302.5
unnamed: TP1492.1, U302.20, U302.21, Z232.2, Z242.1
unnamed: C2512.1, R1532.1, U302.3
unnamed: R1512.2, U302.2
unnamed: C2002.2, C2722.2, U302.15
unnamed: C2462.1, R1472.1, U302.4
unnamed: R1563.1, U303.5
unnamed: TP1493.1, U303.20, U303.21, Z233.2, Z243.1
unnamed: C2513.1, R1533.1, U303.3
unnamed: R1513.2, U303.2
unnamed: C2003.2, C2723.2, U303.15
unnamed: C2463.1, R1473.1, U303.4
OCURLIM_NEG: R22.2, U16.93
OCURLIM_POS: R21.2, U16.95
OCUR_IN: C2.1, R23.1, TP21.1, U3.1, U3.2, U3.13, U3.14, U14.3, U16.2
PRECHARGE_OUT: TP1.1, U16.36
PWM1_N: U11.3, U16.52
PWM1_P: U11.2, U16.67
PWM2_N: U11.5, U16.53
PWM2_P: U11.4, U16.68
PWM3_N: U11.7, U16.54
PWM3_P: U11.6, U16.69
PWM_INHIBIT: U14.4, U16.51
REVER_IN: D5.1, J1.4, R32.2
REV_IN: C30.1, R32.1, R34.2, U16.26
SINA: C60.1, J1.17, R111.1, R112.2
SINB: J1.7, R114.2
SPI1_MISO: U7.7, U16.90
SPI1_MOSI: U11.9, U16.91
SPI1_SCK: U11.8, U16.89
START: D19.1, J1.1, R35.2
START_IN: C31.1, R35.1, R37.2, U16.88
SWCLK: J3.3, U16.76
SWDAT: J3.1, U16.72
T15_IN: D3.1, J1.3, R7.2
T15_OUT: C1.1, R6.2, R7.1, R25.2, U16.25
THROTTLE1: C28.1, R29.1, R3000.2, U16.15
THROTTLE2: C27.1, R2007.1, R2008.2, U16.16
TMPHS1: C78.1, R128.1, ST1.2, U16.33
TMPHS2: C77.1, R129.1, ST3.2, U16.23
TMPHS3: C76.1, R130.1, ST4.2, U16.24
TMPM: C79.1, R132.1, U16.17
UDCIN: C82.1, R237.1, U1.1, U16.18
USART_RX: J4.3, U16.48
USART_TX: J4.4, U16.47
UVLO_IN: R40.2, U16.1

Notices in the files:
ato/layouts/default/default.kicad_pcb:
Copyright 2026
